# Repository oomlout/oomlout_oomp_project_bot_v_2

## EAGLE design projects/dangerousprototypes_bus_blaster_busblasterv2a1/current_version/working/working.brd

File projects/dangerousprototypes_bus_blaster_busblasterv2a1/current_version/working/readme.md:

# bus_blaster
 
## summary 
* id: dangerousprototypes_bus_blaster_busblasterv2a1
* user: dangerousprototypes
* name: bus_blaster
* board: busblasterv2a1
* repo: https://github.com/DangerousPrototypes/Bus_Blaster

* src_file_repo_sch: 
* src_file_repo_sch_link: https://github.com/DangerousPrototypes/Bus_Blaster/tree/master/
* full details link: https://github.com/oomlout/oomlout_oomp_project_bot_v_2/tree/main/projects/dangerousprototypes_bus_blaster_busblasterv2a1/current_version/working

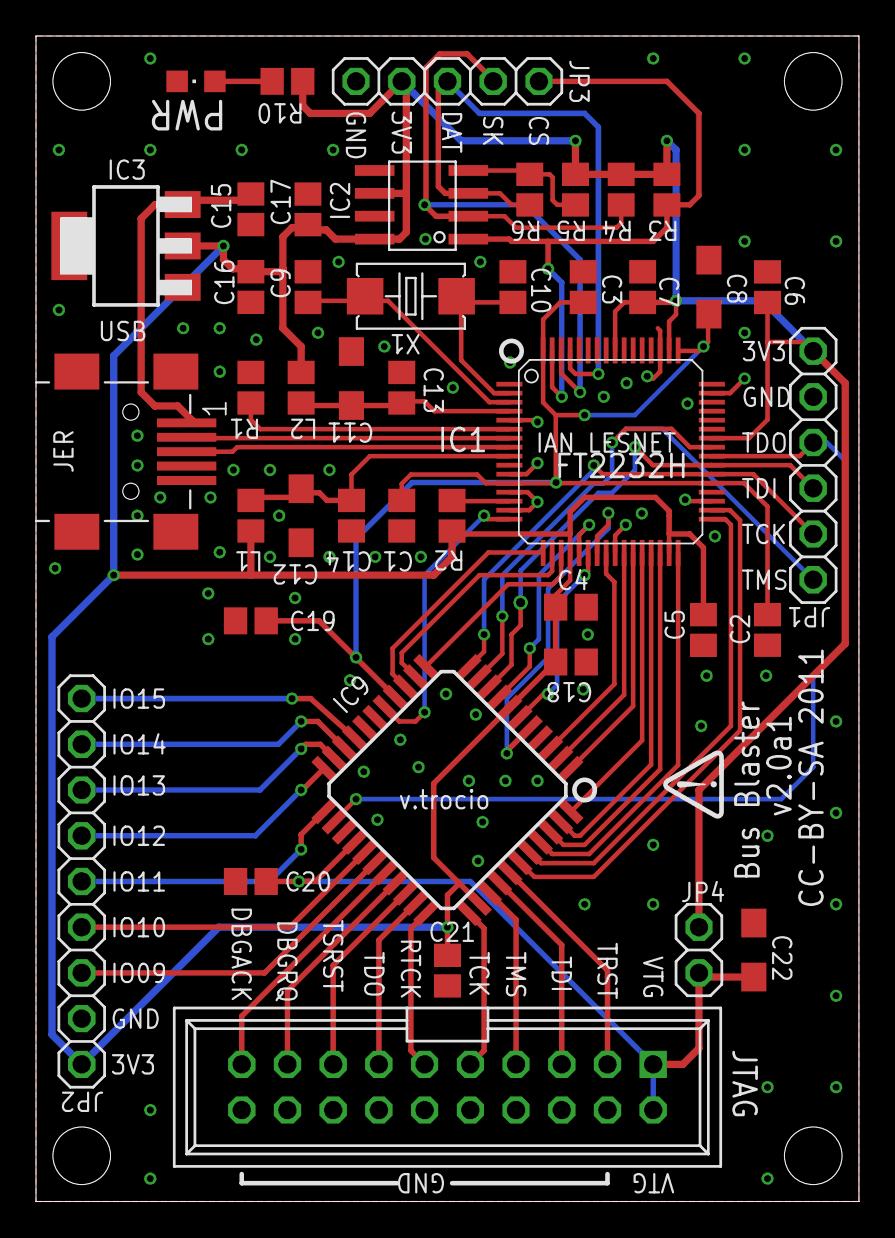
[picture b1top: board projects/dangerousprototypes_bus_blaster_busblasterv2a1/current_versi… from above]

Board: 2 copper layers, 45.7 x 64.8 mm, 45 parts (1 on the bottom side), 54 nets.

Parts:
C1, C2, C3, C4, C5, C6, C7, C13, C14, C15, C16, C17, C18, C19, C20, C21: 100nF; C805
C8: 3.3uF; SMC_A
C9, C10: 27pF; C805
C11, C12, C22: 4.7uF; SMC_A
IC1: FT2232H; LQFP64
IC2: 93C46; SOIC8
IC3: LD1117-3.3; SOT223
IC9: XC2C32A_VQ44_2; VQ44
JP1: 1X06
JP2: 1X09
JP3: 1X05
JP4: 1X02
JTAG: PINHEAD_-_COPY_PINSHRD_PTH_2X10
L1, L2: FB805
PWR: CHIPLED_0805
R1: 12K 1%; R805
R2: 1K; R805
R3, R4, R5: 10K; R805
R6: 2.2K; R805
R10: 470; R805
U$1, U$3: DP_LOGO
USB: CON-USB-MINI-BUSB1; CONN_USB_MINI-B
X1: 12MHz; 4X6

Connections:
1.8V: C1.2, C2.2, C3.2, C8.+, C19.2, IC1.12, IC1.37, IC1.49, IC1.64, IC9.15
+3V3: C4.2, C5.2, C6.2, C7.2, C16.2, C17.2, C18.1, C21.2, IC1.20, IC1.31, IC1.42, IC1.50, IC1.56, IC2.6, IC2.8, IC3.2, IC9.7, IC9.35, JP1.6, JP2.1, JP3.2, JP4.1, L1.2, L2.2, R2.1, R3.2, R4.2, R5.2, R10.2
AC0: IC1.26, IC9.2
AC1: IC1.27, IC9.1
AC2: IC1.28, IC9.44
AC3: IC1.29, IC9.43
AC4: IC1.30, IC9.42
AC5: IC1.32, IC9.41
AC6: IC1.33, IC9.40
AC7: IC1.34, IC9.39
AD0: IC1.16, IC9.16
AD1: IC1.17, IC9.14
AD2: IC1.18, IC9.13
AD3: IC1.19, IC9.12
AD4: IC1.21, IC9.8
AD5: IC1.22, IC9.6
AD6: IC1.23, IC9.5
AD7: IC1.24, IC9.3
BD0: IC1.38, IC9.11, JP1.2
BD1: IC1.39, IC9.9, JP1.3
BD2: IC1.40, IC9.24, JP1.4
BD3: IC1.41, IC9.10, JP1.1
CS: IC1.63, IC2.1, JP3.5, R3.1
DATA: IC1.61, IC2.3, JP3.3, R6.1
DBGACK1: IC9.29, JTAG.19
DBGRQ1: IC9.30, JTAG.17
DM: IC1.7, USB.D-
DO: IC2.4, R5.1, R6.2
DP: IC1.8, USB.D+
GND: C1.1, C2.1, C3.1, C4.1, C5.1, C6.1, C7.1, C8.-, C9.2, C10.2, C11.-, C12.-, C13.1, C14.1, C15.1, C16.1, C17.1, C18.2, C19.1, C20.1, C21.1, C22.-, IC1.1, IC1.5, IC1.10, IC1.11, IC1.13, IC1.15, IC1.25, IC1.35, IC1.47, IC1.51, IC2.5, IC2.7, IC3.1, IC9.4, IC9.17, IC9.18, IC9.25, JP1.5, JP2.2, JP3.1, JTAG.4, JTAG.6, JTAG.8, JTAG.10, JTAG.12, JTAG.14, JTAG.16, JTAG.18, JTAG.20, PWR.C, R1.1, USB.GND
IO9: IC9.28, JP2.3
IO10: IC9.27, JP2.4
IO11: IC9.23, JP2.5
IO12: IC9.22, JP2.6
IO13: IC9.21, JP2.7
IO14: IC9.20, JP2.8
IO15: IC9.19, JP2.9
unnamed: C9.1, IC1.3, X1.2
unnamed: C10.1, IC1.2, X1.1
unnamed: IC1.14, R2.2
unnamed: IC1.6, R1.2
unnamed: C15.2, IC3.3, USB.VUSB
unnamed: PWR.A, R10.1
RTCK1: IC9.33, JTAG.11
SK: IC1.62, IC2.2, JP3.4, R4.1
TCK1: IC9.34, JTAG.9
TDI1: IC9.37, JTAG.5
TDO1: IC9.32, JTAG.13
TMS1: IC9.36, JTAG.7
TRST1: IC9.38, JTAG.3
TSRST1: IC9.31, JTAG.15
VPHY: C11.+, C13.2, IC1.4, L2.1
VPLL: C12.+, C14.2, IC1.9, L1.1
V_TARGET: C20.2, C22.+, IC9.26, JP4.2, JTAG.1, JTAG.2

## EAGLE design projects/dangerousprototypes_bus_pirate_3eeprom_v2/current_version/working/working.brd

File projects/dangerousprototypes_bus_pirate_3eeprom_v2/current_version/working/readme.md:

# bus_pirate
 
## summary 
* id: dangerousprototypes_bus_pirate_3eeprom_v2
* user: dangerousprototypes
* name: bus_pirate
* board: 3eeprom_v2
* repo: https://github.com/DangerousPrototypes/Bus_Pirate

* src_file_repo_sch: 
* src_file_repo_sch_link: https://github.com/DangerousPrototypes/Bus_Pirate/tree/master/
* full details link: https://github.com/oomlout/oomlout_oomp_project_bot_v_2/tree/main/projects/dangerousprototypes_bus_pirate_3eeprom_v2/current_version/working

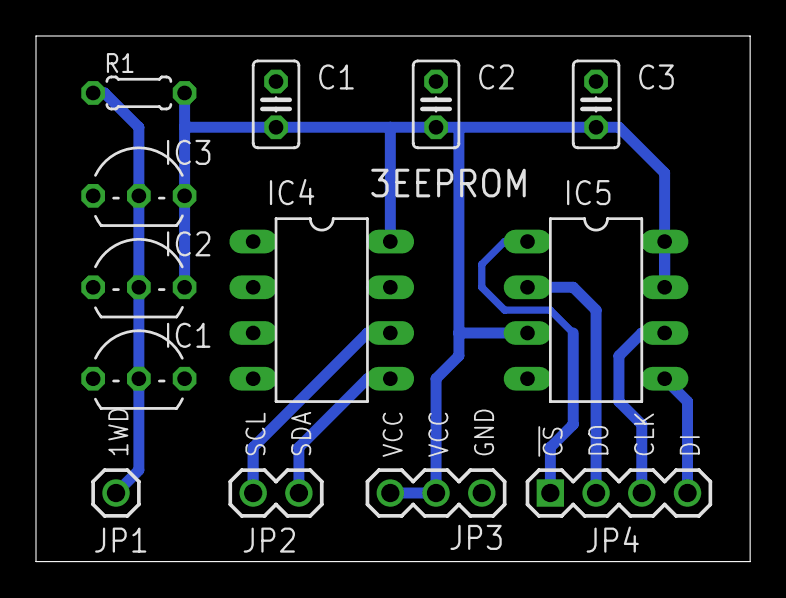
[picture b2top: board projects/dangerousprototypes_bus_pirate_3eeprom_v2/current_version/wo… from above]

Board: 2 copper layers, 39.7 x 29.2 mm, 13 parts (0 on the bottom side), 9 nets.

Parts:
C1, C2, C3: 0.1uF; C025-025X050
IC1: DS2431; TO92-
IC2, IC3: DS1822; TO92-
IC4: 24AAxx; DIL8
IC5: 25AAxx; DIL8
JP1: M01PTH; 1X01
JP2: 1X02
JP3: 1X03
JP4: 1X04
R1: 1K8; 0204/5

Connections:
+5V: C1.1, C2.1, C3.1, IC2.3, IC3.3, IC4.8, IC5.3, IC5.7, IC5.8, JP3.2, JP3.3, R1.2
GND: C1.2, C2.2, C3.2, IC1.1, IC2.1, IC3.1, IC4.1, IC4.2, IC4.3, IC4.4, IC4.7, IC5.4, JP3.1
unnamed: IC5.1, JP4.1
unnamed: IC5.2, JP4.2
unnamed: IC4.6, JP2.1
unnamed: IC4.5, JP2.2
unnamed: IC5.5, JP4.4
unnamed: IC5.6, JP4.3
unnamed: IC1.2, IC2.2, IC3.2, JP1.1, R1.1

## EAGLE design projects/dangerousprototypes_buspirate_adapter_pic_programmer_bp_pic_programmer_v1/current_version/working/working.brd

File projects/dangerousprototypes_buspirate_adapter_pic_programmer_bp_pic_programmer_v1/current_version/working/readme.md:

# buspirate_adapter_pic_programmer
 
## summary 
* id: dangerousprototypes_buspirate_adapter_pic_programmer_bp_pic_programmer_v1
* user: dangerousprototypes
* name: buspirate_adapter_pic_programmer
* board: bp_pic_programmer_v1
* repo: https://github.com/DangerousPrototypes/Buspirate_Adapter_Pic_Programmer

* src_file_repo_sch: 
* src_file_repo_sch_link: https://github.com/DangerousPrototypes/Buspirate_Adapter_Pic_Programmer/tree/master/
* full details link: https://github.com/oomlout/oomlout_oomp_project_bot_v_2/tree/main/projects/dangerousprototypes_buspirate_adapter_pic_programmer_bp_pic_programmer_v1/current_version/working

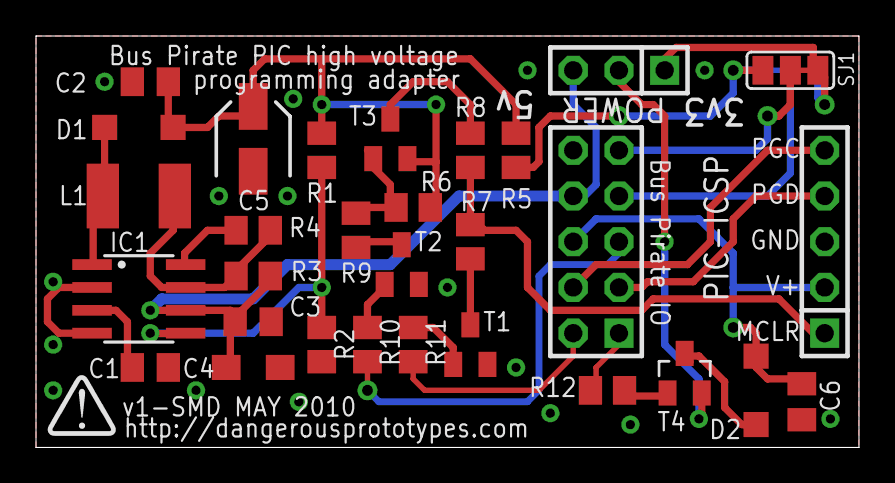
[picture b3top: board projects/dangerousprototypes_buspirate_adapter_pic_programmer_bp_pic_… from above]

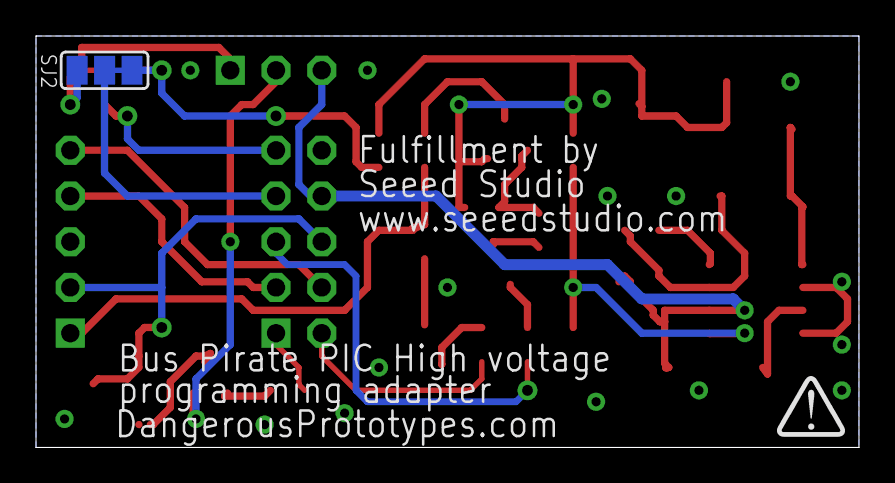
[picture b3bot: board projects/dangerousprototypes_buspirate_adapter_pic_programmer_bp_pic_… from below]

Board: 2 copper layers, 45.7 x 22.9 mm, 33 parts (2 on the bottom side), 28 nets.

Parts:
C1: 270pF; C0805K
C2, C6: 0.1uF/50V; C0805K
C3: 0.1uF; C0805K
C4: 10uF; SMC_A
C5: 4.7uF/35V; SANYO-OSCON_SMD_A5
D1, D2: 1N5819; SOD123
IC1: MC34063AD; SO08
JP1: 2X05
L1: 680uH/0.012A; L4532P
PIC-ICSP: 1X05
POWER: 1X03
R1: 20K; M0805
R2, R12: 2K2; M0805
R3: 4R7; M0805
R4: 180R; M0805
R5: 39K; M0805
R6: 100K; M0805
R7: 100R; M0805
R8, R9, R10, R11: 10K; M0805
SJ1, SJ2: SJ_2
T1, T2: BC818-16SMD; SOT23-BEC
T3: MMBTA56-SOT23; SOT23
T4: TSM2301CX; SOT23
U$1, U$2: DP-LOGO

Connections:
3V3: POWER.1, SJ1.3, SJ2.3
3V3(V3)ADC(V2GO): JP1.9, SJ1.2
5V: C3.1, C4.+, IC1.6, JP1.8, POWER.3, R3.1
13V: C2.1, C5.+, D1.C, R1.1, R5.2, R6.2, T3.2
ADC: R5.1, SJ1.1, SJ2.1
ADC(V3)3V3(V2GO): JP1.7, SJ2.2
GND: C1.2, C2.2, C3.2, C4.-, C5.-, C6.2, IC1.2, IC1.4, JP1.10, PIC-ICSP.3, R2.2, T1.E, T2.E
MCLR: JP1.2, R11.1
MISO: JP1.1, R12.1
unnamed: R12.2, T4.1
unnamed: R7.1, T1.C
unnamed: R8.2, T3.3
unnamed: R9.1, T2.C
unnamed: R6.1, R9.2, T3.1
unnamed: R11.2, T1.B
unnamed: R10.2, T2.B
unnamed: IC1.8, R4.1
unnamed: D2.A, T4.3
unnamed: IC1.7, L1.2, R3.2, R4.2
unnamed: IC1.5, R1.2, R2.1
unnamed: D1.A, IC1.1, L1.1
unnamed: C1.1, IC1.3
PGC: JP1.4, PIC-ICSP.5
PGD: JP1.3, PIC-ICSP.4
VDD_SWITCH: POWER.2, T4.2
VPP: PIC-ICSP.1, R7.2, R8.1
VPPEN: JP1.5, R10.1
VTARGET: C6.1, D2.C, JP1.6, PIC-ICSP.2

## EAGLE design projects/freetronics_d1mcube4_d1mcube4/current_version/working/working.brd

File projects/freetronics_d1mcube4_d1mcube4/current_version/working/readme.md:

# d1mcube4
 
## summary 
* id: freetronics_d1mcube4_d1mcube4
* user: freetronics
* name: d1mcube4
* board: d1mcube4
* repo: https://github.com/freetronics/D1MCUBE4

* src_file_repo_sch: 
* src_file_repo_sch_link: https://github.com/freetronics/D1MCUBE4/tree/master/
* full details link: https://github.com/oomlout/oomlout_oomp_project_bot_v_2/tree/main/projects/freetronics_d1mcube4_d1mcube4/current_version/working

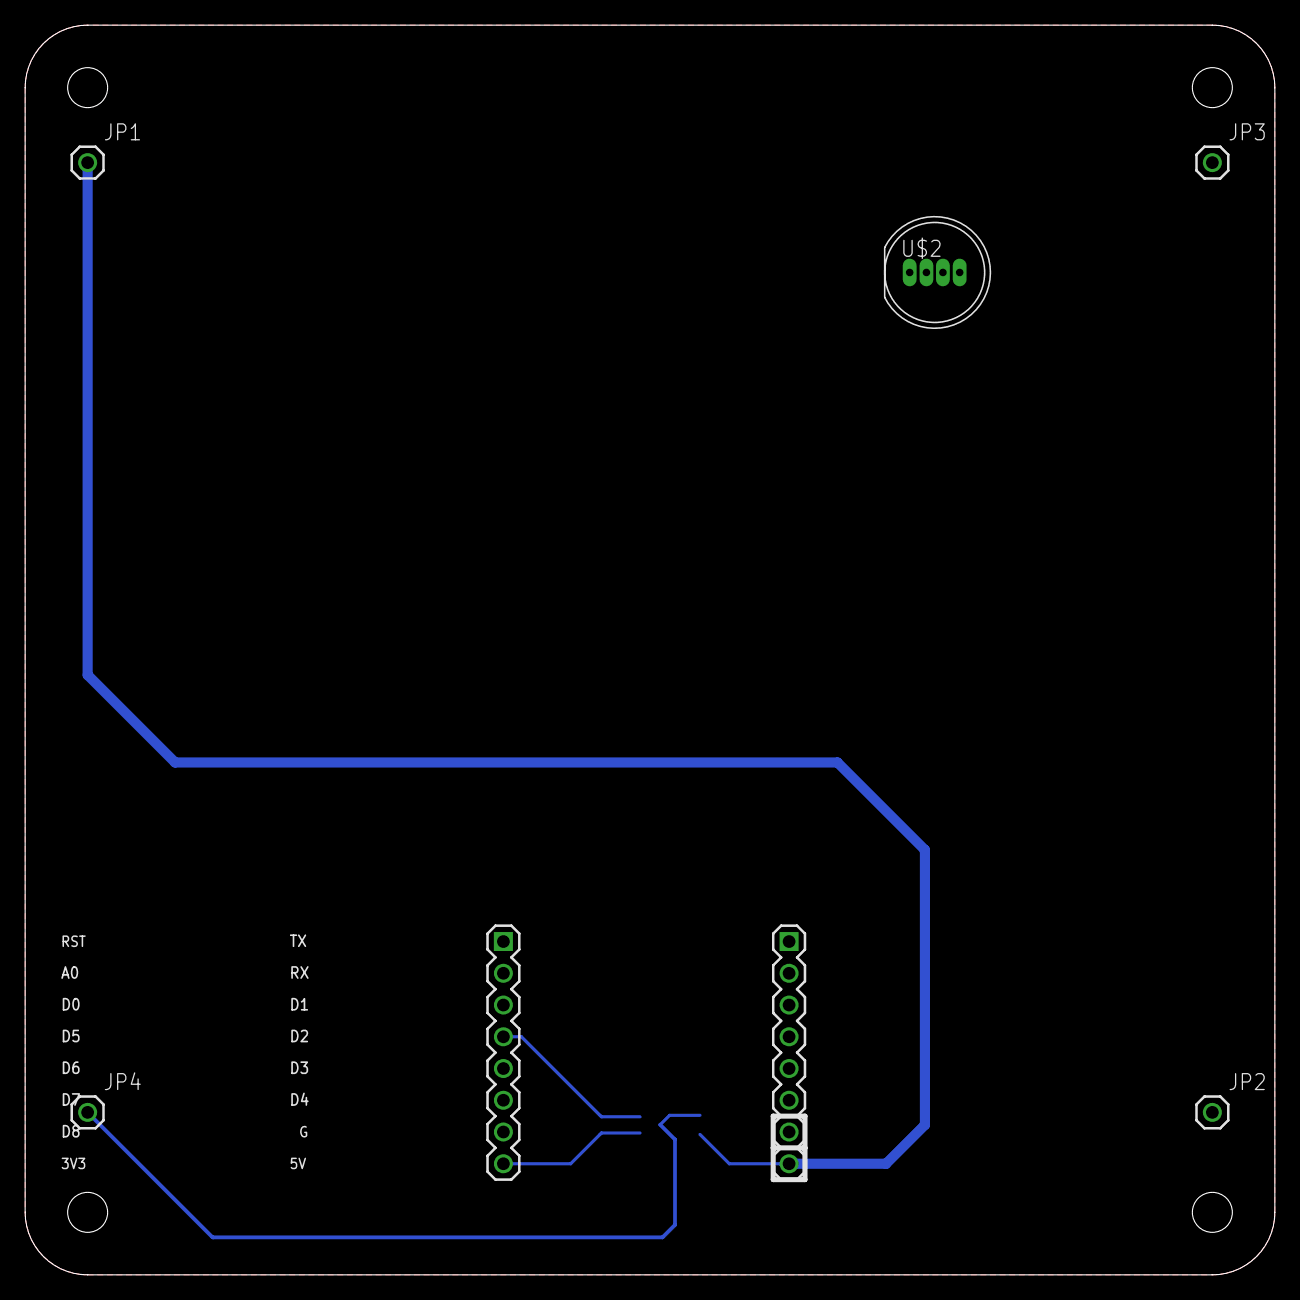
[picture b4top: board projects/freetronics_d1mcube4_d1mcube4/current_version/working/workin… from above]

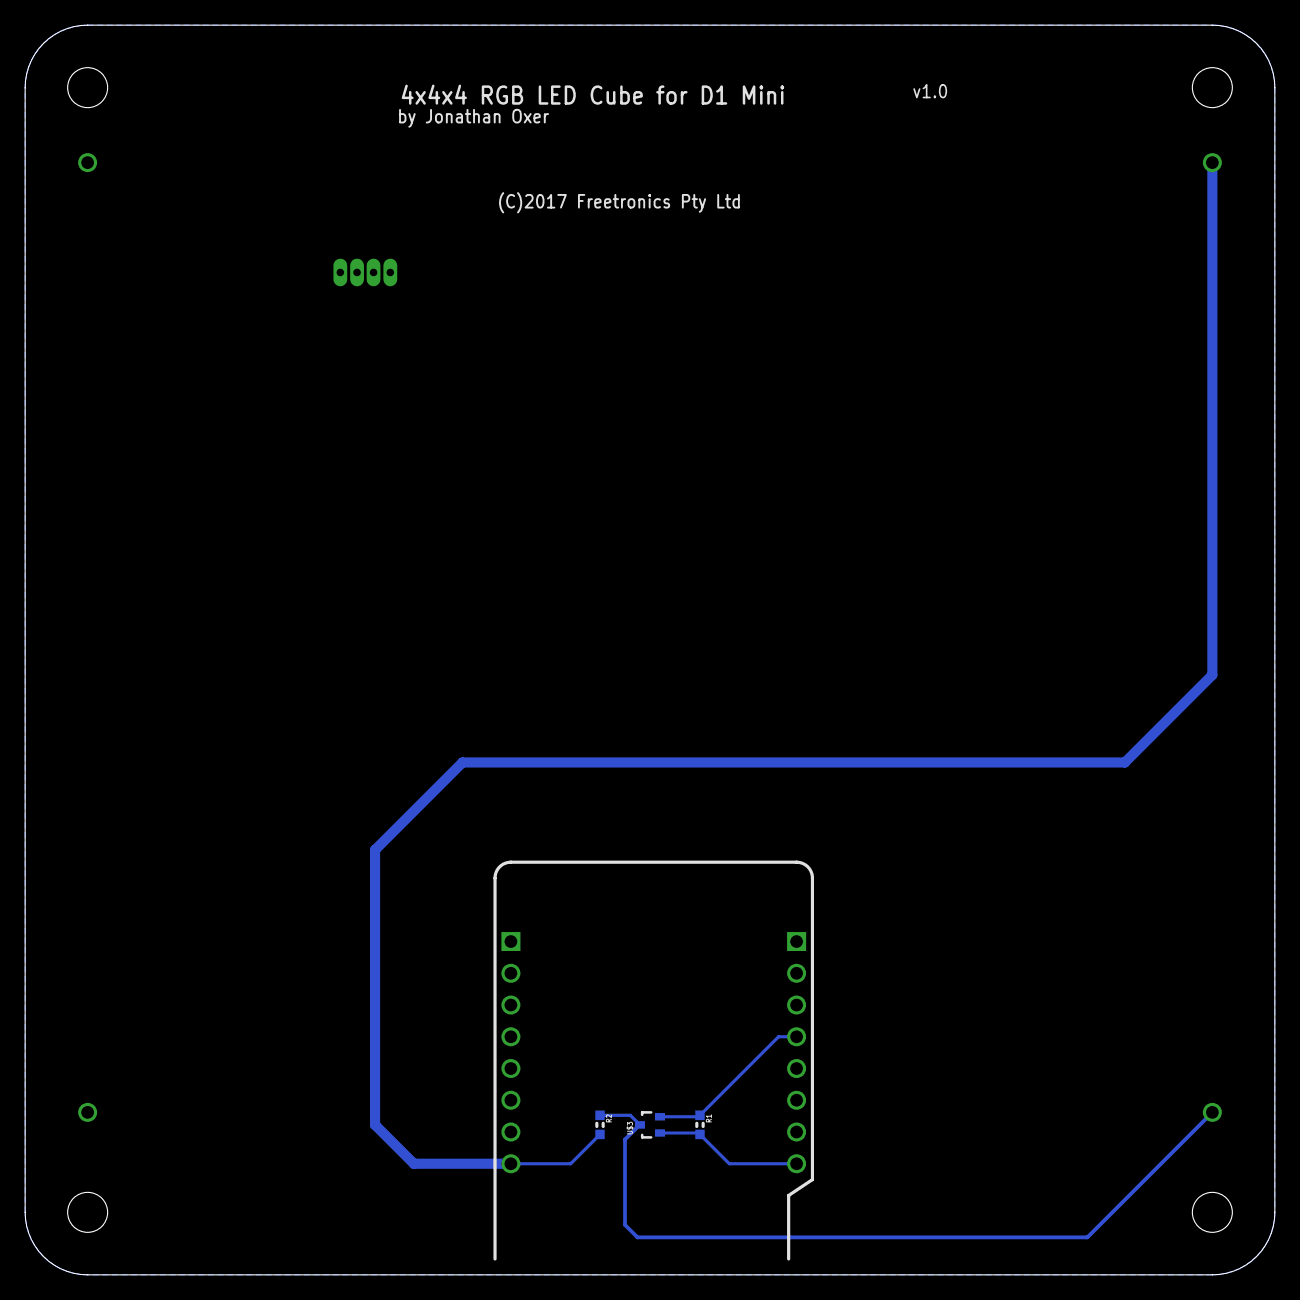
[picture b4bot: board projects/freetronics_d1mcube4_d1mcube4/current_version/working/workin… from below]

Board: 2 copper layers, 100.0 x 100.0 mm, 10 parts (3 on the bottom side), 5 nets.

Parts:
H1, H2: 1X08
JP1, JP2, JP3, JP4: M01PTH; 1X01
R1, R2: 10k; 0603
U$2: APA106F8; LED8MMRGB
U$3: RJU003N03; SOT32-3

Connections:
3.3V: H1.8, R1.2, U$3.1
5V: H2.8, JP1.1, R2.2
D5: H1.4, R1.1, U$3.2
DATA: JP4.1, R2.1, U$3.3
GND: H2.7, JP2.1, JP3.1, U$2.2

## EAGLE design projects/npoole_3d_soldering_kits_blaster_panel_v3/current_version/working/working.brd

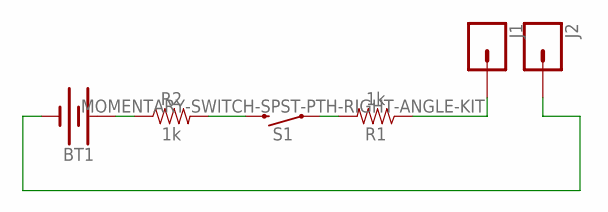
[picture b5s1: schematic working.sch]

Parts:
BT1: BATTERY-20MM_SMD_4LEGS; BATTCON_20MM_4LEGS
J1, J2: CONN_01; 1X01
R1, R2: 1k; AXIAL-0.3
S1: MOMENTARY-SWITCH-SPST-PTH-RIGHT-ANGLE-KIT; TACTILE_SWITCH_PTH_RIGHT_ANGLE_KIT

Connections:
unnamed: R2.P$2 (2), S1.2
unnamed: R1.P$2 (2), S1.1
unnamed: J1.1, R1.P$1 (1)
unnamed: BT1.NEGATIVE (-), J2.1
unnamed: BT1.POSITIVE@1 (+), BT1.POSITIVE@2 (+), BT1.POSITIVE@3 (+), BT1.POSITIVE@4 (+), R2.P$1 (1)

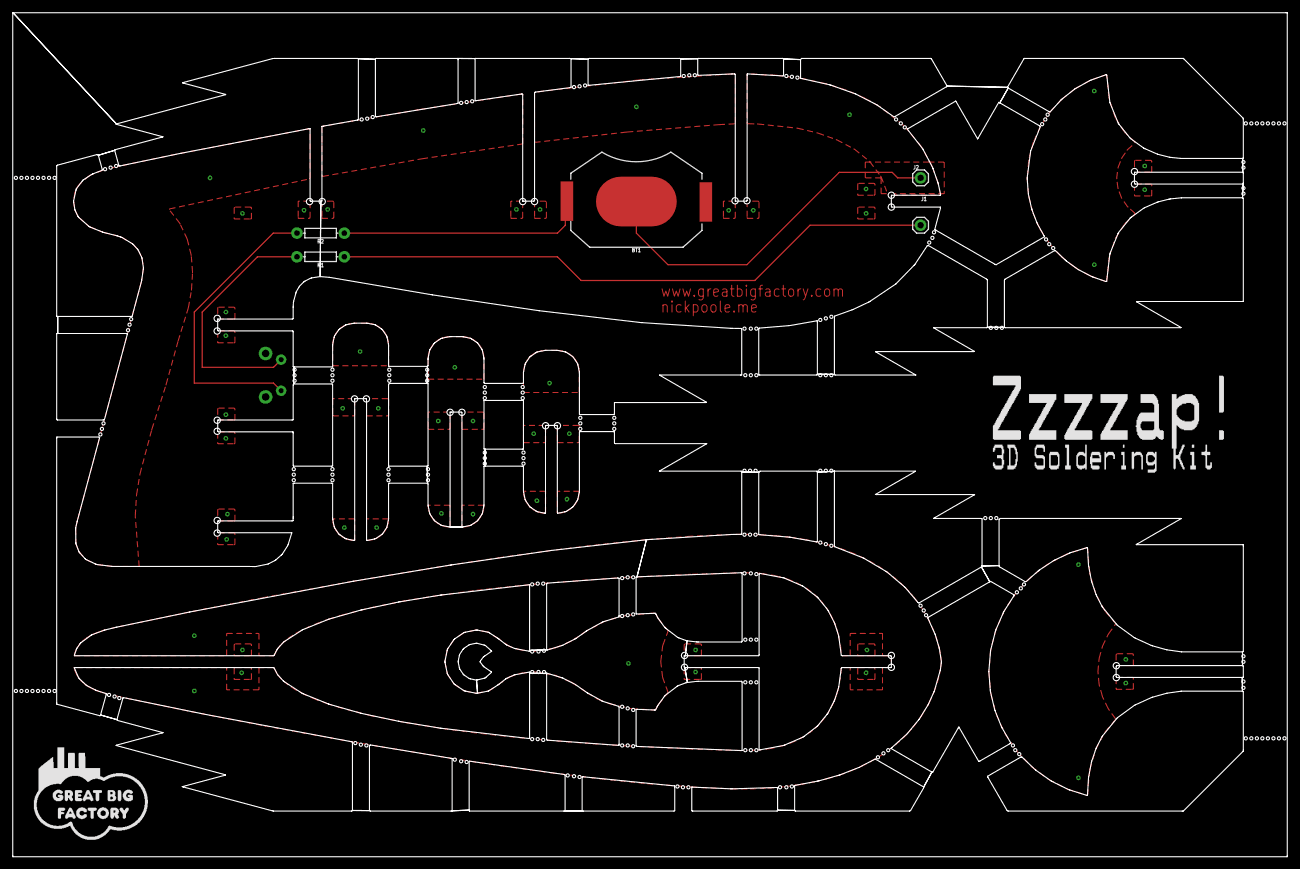
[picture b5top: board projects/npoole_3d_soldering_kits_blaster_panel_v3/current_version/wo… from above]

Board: 2 copper layers, 205.0 x 135.8 mm, 8 parts (1 on the bottom side), 5 nets.

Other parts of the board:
E$1: GREATBIGFACTORYCLOUDLOGO#PNG
U$1: TEXT345#PNG

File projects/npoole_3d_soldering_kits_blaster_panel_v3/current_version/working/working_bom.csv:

"Id";"Designator";"Footprint";"Quantity";"Designation";"Supplier and ref";
1;"@HOLE20,@HOLE8,@HOLE134,@HOLE54,@HOLE166,@HOLE176,@HOLE216,@HOLE157,@HOLE70,@HOLE173,@HOLE236,@HOLE16,@HOLE103,@HOLE145,@HOLE208,@HOLE147,@HOLE37,@HOLE184,@HOLE240,@HOLE138,@HOLE17,@HOLE44,@HOLE24,@HOLE28,@HOLE160,@HOLE117,@HOLE25,@HOLE74,@HOLE239,@HOLE217,@HOLE214,@HOLE213,@HOLE237,@HOLE82,@HOLE142,@HOLE120,@HOLE137,@HOLE234,@HOLE39,@HOLE152,@HOLE66,@HOLE95,@HOLE194,@HOLE198,@HOLE182,@HOLE185,@HOLE193,@HOLE121,@HOLE87,@HOLE215,@HOLE183,@HOLE12,@HOLE69,@HOLE62,@HOLE132,@HOLE211,@HOLE169,@HOLE190,@HOLE94,@HOLE90,@HOLE104,@HOLE158,@HOLE33,@HOLE68,@HOLE0,@HOLE45,@HOLE57,@HOLE238,@HOLE170,@HOLE21,@HOLE187,@HOLE92,@HOLE77,@HOLE151,@HOLE123,@HOLE72,@HOLE52,@HOLE226,@HOLE202,@HOLE210,@HOLE65,@HOLE110,@HOLE206,@HOLE212,@HOLE18,@HOLE186,@HOLE47,@HOLE203,@HOLE165,@HOLE177,@HOLE75,@HOLE15,@HOLE23,@HOLE153,@HOLE84,@HOLE81,@HOLE108,@HOLE107,@HOLE150,@HOLE136,@HOLE11,@HOLE163,@HOLE10,@HOLE31,@HOLE48,@HOLE83,@HOLE96,@HOLE178,@HOLE9,@HOLE101,@HOLE102,@HOLE241,@HOLE51,@HOLE223,@HOLE172,@HOLE122,@HOLE219,@HOLE209,@HOLE7,@HOLE116,@HOLE56,@HOLE105,@HOLE118,@HOLE34,@HOLE38,@HOLE235,@HOLE230,@HOLE231,@HOLE164,@HOLE97,@HOLE40,@HOLE127,@HOLE124,@HOLE205,@HOLE168,@HOLE115,@HOLE2,@HOLE80,@HOLE29,@HOLE144,@HOLE159,@HOLE3,@HOLE106,@HOLE53,@HOLE61,@HOLE155,@HOLE200,@HOLE35,@HOLE4,@HOLE228,@HOLE148,@HOLE196,@HOLE207,@HOLE129,@HOLE146,@HOLE125,@HOLE218,@HOLE119,@HOLE175,@HOLE130,@HOLE59,@HOLE233,@HOLE63,@HOLE191,@HOLE13,@HOLE201,@HOLE86,@HOLE181,@HOLE100,@HOLE154,@HOLE131,@HOLE220,@HOLE67,@HOLE99,@HOLE41,@HOLE180,@HOLE188,@HOLE171,@HOLE46,@HOLE1,@HOLE76,@HOLE204,@HOLE174,@HOLE128,@HOLE71,@HOLE197,@HOLE98,@HOLE222,@HOLE79,@HOLE232,@HOLE30,@HOLE93,@HOLE14,@HOLE64,@HOLE162,@HOLE161,@HOLE139,@HOLE135,@HOLE224,@HOLE88,@HOLE89,@HOLE78,@HOLE91,@HOLE227,@HOLE32,@HOLE195,@HOLE26,@HOLE126,@HOLE27,@HOLE36,@HOLE60,@HOLE199,@HOLE192,@HOLE114,@HOLE133,@HOLE189,@HOLE42,@HOLE167,@HOLE225,@HOLE111,@HOLE141,@HOLE49,@HOLE179,@HOLE85,@HOLE112,@HOLE221,@HOLE149,@HOLE113,@HOLE55,@HOLE109,@HOLE19,@HOLE50,@HOLE73,@HOLE156,@HOLE6,@HOLE58,@HOLE143,@HOLE140,@HOLE43,@HOLE5,@HOLE229,@HOLE22";"";242;"";;;
2;"J2,J1";"1X01";2;"";;;
3;"E$1";"GREATBIGFACTORYCLOUDLOGO#PNG";1;"";;;
4;"U$1";"TEXT345#PNG";1;"";;;
5;"R1,R2";"AXIAL-0.3";2;"1k";;;
6;"BT1";"BATTCON_20MM_4LEGS";1;"";;;
7;"S1";"TACTILE_SWITCH_PTH_RIGHT_ANGLE_KIT";1;"MOMENTARY-SWITCH-SPST-PTH-RIGHT-ANGLE-KIT";;;

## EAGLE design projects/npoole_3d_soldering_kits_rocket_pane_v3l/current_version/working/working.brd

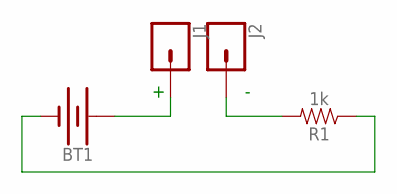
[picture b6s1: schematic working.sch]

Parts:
BT1: BATTERY-20MM_SMD_4LEGS; BATTCON_20MM_4LEGS
J1, J2: CONN_01; 1X01
R1: 1k; AXIAL-0.3

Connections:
unnamed: BT1.POSITIVE@1 (+), BT1.POSITIVE@2 (+), BT1.POSITIVE@3 (+), BT1.POSITIVE@4 (+), J1.1
unnamed: J2.1, R1.P$2 (2)
unnamed: BT1.NEGATIVE (-), R1.P$1 (1)

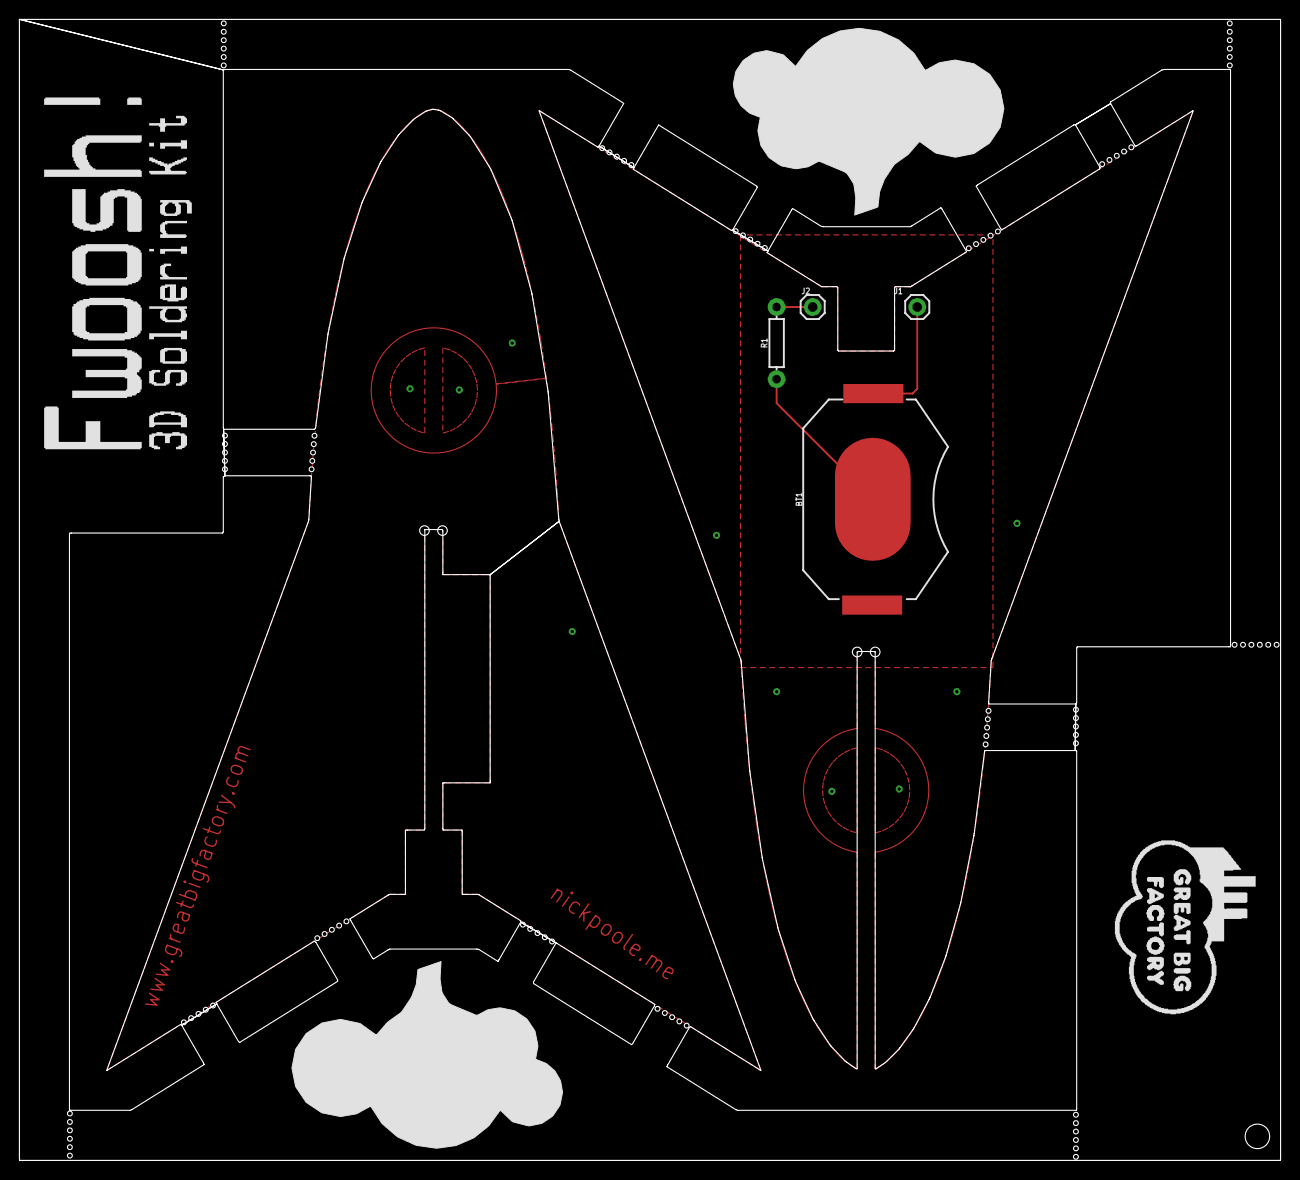
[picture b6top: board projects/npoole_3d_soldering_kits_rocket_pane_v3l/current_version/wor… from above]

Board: 2 copper layers, 133.3 x 120.6 mm, 6 parts (0 on the bottom side), 3 nets.

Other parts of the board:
U$1: TEXT1466#PNG
U$2: GREATBIGFACTORYCLOUDLOGO#PNG

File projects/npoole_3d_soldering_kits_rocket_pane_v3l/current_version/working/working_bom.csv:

"Id";"Designator";"Footprint";"Quantity";"Designation";"Supplier and ref";
1;"@HOLE72,@HOLE63,@HOLE25,@HOLE85,@HOLE20,@HOLE17,@HOLE7,@HOLE42,@HOLE31,@HOLE70,@HOLE1,@HOLE32,@HOLE18,@HOLE49,@HOLE12,@HOLE64,@HOLE8,@HOLE89,@HOLE59,@HOLE4,@HOLE30,@HOLE29,@HOLE9,@HOLE80,@HOLE23,@HOLE83,@HOLE2,@HOLE33,@HOLE60,@HOLE41,@HOLE82,@HOLE56,@HOLE0,@HOLE90,@HOLE77,@HOLE19,@HOLE10,@HOLE43,@HOLE22,@HOLE15,@HOLE62,@HOLE58,@HOLE73,@HOLE57,@HOLE36,@HOLE27,@HOLE75,@HOLE66,@HOLE92,@HOLE45,@HOLE13,@HOLE94,@HOLE81,@HOLE68,@HOLE44,@HOLE3,@HOLE87,@HOLE24,@HOLE38,@HOLE61,@HOLE35,@HOLE88,@HOLE34,@HOLE76,@HOLE37,@HOLE11,@HOLE71,@HOLE5,@HOLE78,@HOLE53,@HOLE93,@HOLE28,@HOLE6,@HOLE54,@HOLE48,@HOLE51,@HOLE50,@HOLE79,@HOLE69,@HOLE84,@HOLE52,@HOLE91,@HOLE39,@HOLE47,@HOLE74,@HOLE21,@HOLE14,@HOLE65,@HOLE67,@HOLE16,@HOLE55,@HOLE40,@HOLE46,@HOLE86,@HOLE26";"";95;"";;;
2;"J1,J2";"1X01";2;"";;;
3;"U$1";"TEXT1466#PNG";1;"";;;
4;"U$2";"GREATBIGFACTORYCLOUDLOGO#PNG";1;"";;;
5;"R1";"AXIAL-0.3";1;"1k";;;
6;"BT1";"BATTCON_20MM_4LEGS";1;"";;;

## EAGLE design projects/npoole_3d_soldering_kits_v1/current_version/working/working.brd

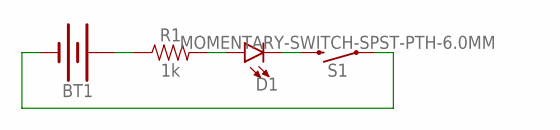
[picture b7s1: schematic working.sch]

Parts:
BT1: BATTERY-20MM_SMD_4LEGS; BATTCON_20MM_4LEGS
D1: LED5MM; LED_5MM
R1: 1k; AXIAL-0.3
S1: MOMENTARY-SWITCH-SPST-PTH-6.0MM; TACTILE_SWITCH_PTH_6.0MM

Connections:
unnamed: BT1.POSITIVE@1 (+), BT1.POSITIVE@2 (+), BT1.POSITIVE@3 (+), BT1.POSITIVE@4 (+), R1.P$1 (1)
unnamed: D1.A, R1.P$2 (2)
unnamed: D1.K (C), S1.3 (2)
unnamed: BT1.NEGATIVE (-), S1.1

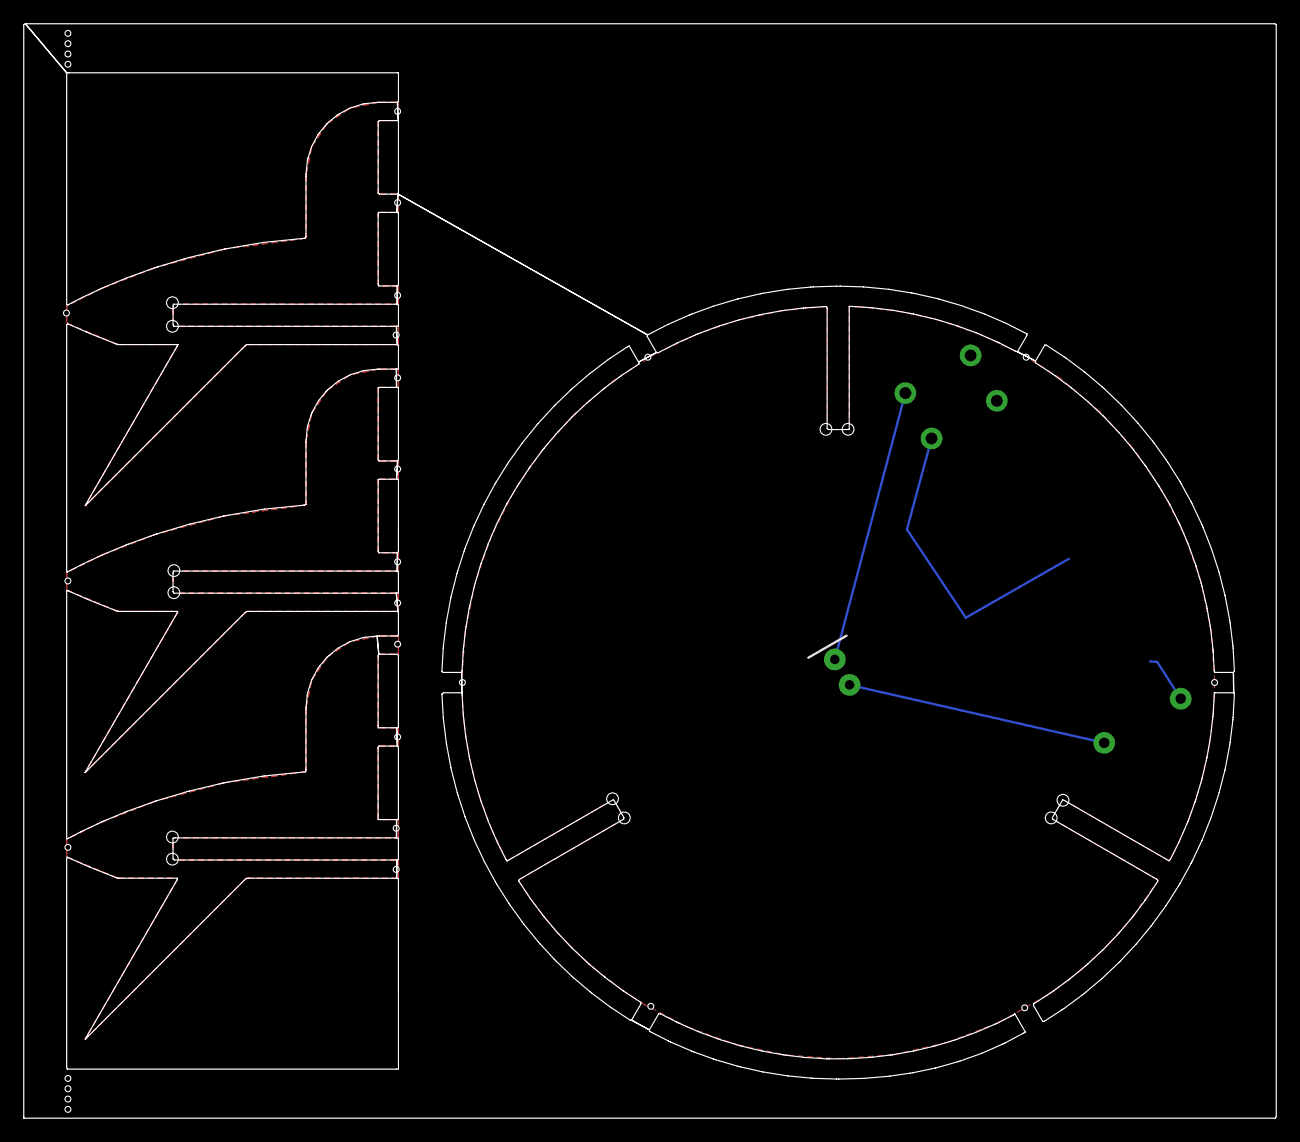
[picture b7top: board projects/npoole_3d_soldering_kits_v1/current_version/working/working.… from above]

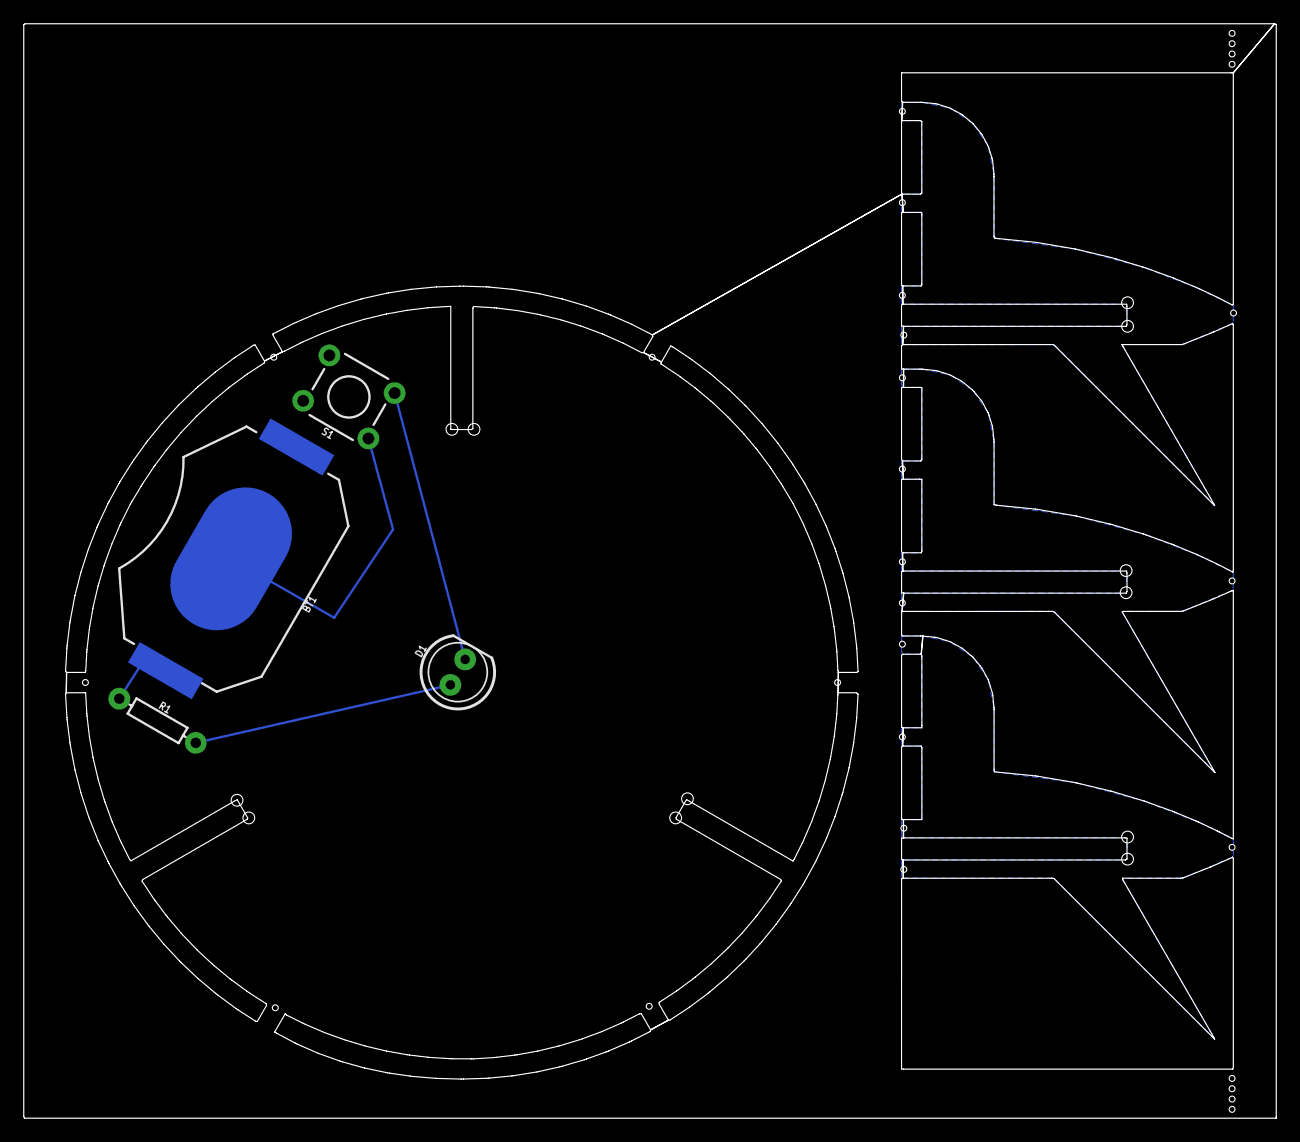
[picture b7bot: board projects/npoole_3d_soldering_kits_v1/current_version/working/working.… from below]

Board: 2 copper layers, 108.1 x 94.4 mm, 4 parts (4 on the bottom side), 4 nets.

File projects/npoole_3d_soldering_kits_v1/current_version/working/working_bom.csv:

"Id";"Designator";"Footprint";"Quantity";"Designation";"Supplier and ref";
1;"@HOLE23,@HOLE17,@HOLE12,@HOLE29,@HOLE19,@HOLE13,@HOLE5,@HOLE38,@HOLE14,@HOLE3,@HOLE24,@HOLE22,@HOLE34,@HOLE37,@HOLE21,@HOLE36,@HOLE39,@HOLE4,@HOLE11,@HOLE33,@HOLE25,@HOLE28,@HOLE27,@HOLE10,@HOLE15,@HOLE1,@HOLE30,@HOLE2,@HOLE35,@HOLE0,@HOLE32,@HOLE31,@HOLE8,@HOLE7,@HOLE9,@HOLE18,@HOLE40,@HOLE6,@HOLE16,@HOLE20,@HOLE26";"";41;"";;;
2;"BT1";"BATTCON_20MM_4LEGS";1;"";;;
3;"R1";"AXIAL-0.3";1;"1k";;;
4;"D1";"LED_5MM";1;"";;;
5;"S1";"TACTILE_SWITCH_PTH_6.0MM";1;"MOMENTARY-SWITCH-SPST-PTH-6.0MM";;;

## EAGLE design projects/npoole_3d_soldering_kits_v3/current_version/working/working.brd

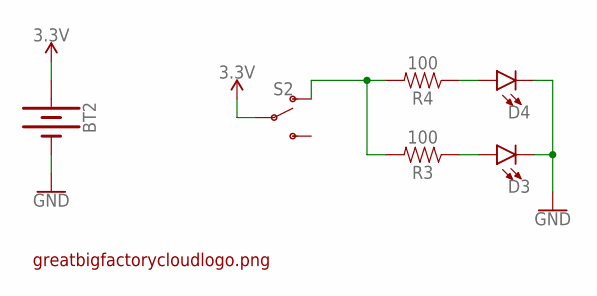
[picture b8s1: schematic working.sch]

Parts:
BT2: BATTERY-20MM_PTH_KIT; BATTCOM_20MM_PTH_KIT
D3, D4: LED5MM; LED_5MM
R3, R4: 100; AXIAL-0.3EZ
S2: SWITCH-SPDT-PTH-11.6X4.0MM-KIT; SWITCH_SPDT_PTH_11.6X4.0MM_KIT
U$1: GREATBIGFACTORYCLOUDLOGO#PNG

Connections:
3.3V: BT2.1 (+), S2.2
GND: BT2.2 (-), D3.K (C), D4.K (C)
unnamed: R3.P$2 (2), R4.P$2 (2), S2.1 (O)
unnamed: D4.A, R4.P$1 (1)
unnamed: D3.A, R3.P$1 (1)

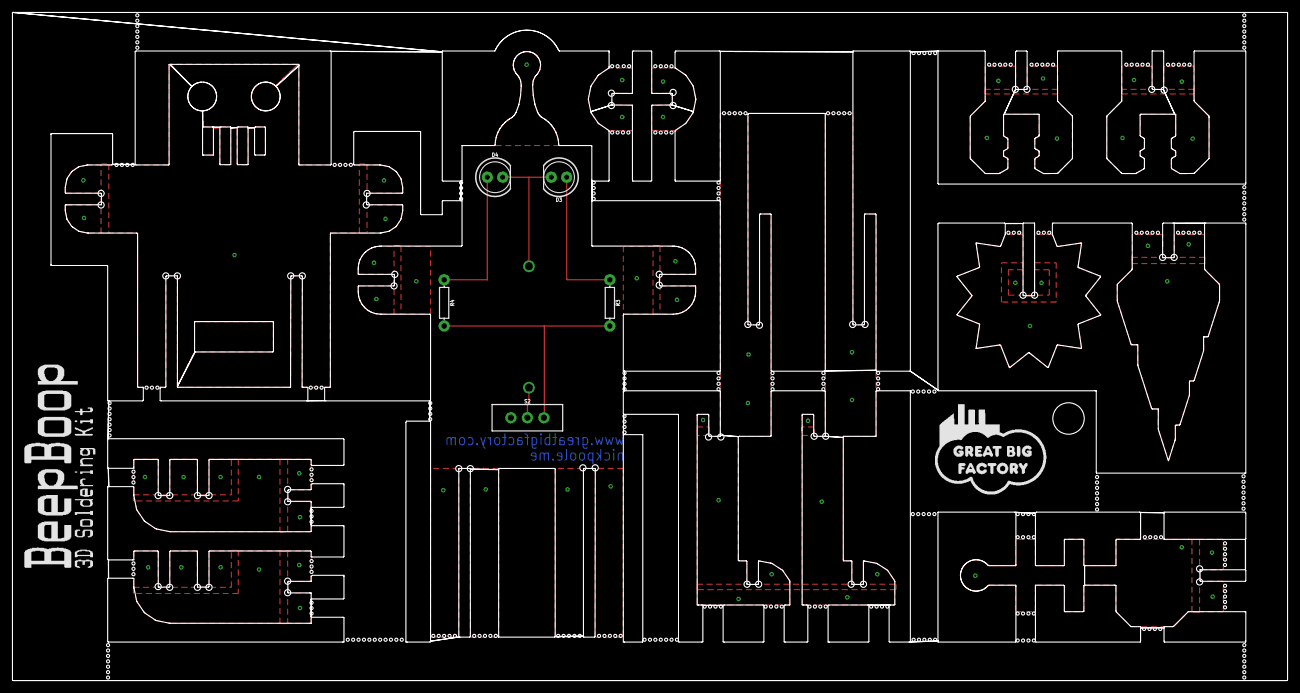
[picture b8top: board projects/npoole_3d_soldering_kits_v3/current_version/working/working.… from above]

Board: 2 copper layers, 210.1 x 110.1 mm, 8 parts (1 on the bottom side), 5 nets.

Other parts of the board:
U$2: RECT1468#PNG

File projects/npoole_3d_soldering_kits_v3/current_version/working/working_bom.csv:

"Id";"Designator";"Footprint";"Quantity";"Designation";"Supplier and ref";
1;"@HOLE198,@HOLE122,@HOLE124,@HOLE74,@HOLE68,@HOLE293,@HOLE29,@HOLE268,@HOLE221,@HOLE226,@HOLE330,@HOLE295,@HOLE11,@HOLE0,@HOLE292,@HOLE49,@HOLE169,@HOLE306,@HOLE328,@HOLE65,@HOLE195,@HOLE93,@HOLE17,@HOLE213,@HOLE69,@HOLE199,@HOLE212,@HOLE339,@HOLE319,@HOLE321,@HOLE345,@HOLE323,@HOLE96,@HOLE190,@HOLE119,@HOLE149,@HOLE239,@HOLE55,@HOLE252,@HOLE281,@HOLE249,@HOLE51,@HOLE137,@HOLE34,@HOLE223,@HOLE6,@HOLE318,@HOLE114,@HOLE154,@HOLE176,@HOLE66,@HOLE23,@HOLE151,@HOLE141,@HOLE348,@HOLE121,@HOLE326,@HOLE184,@HOLE274,@HOLE225,@HOLE344,@HOLE165,@HOLE88,@HOLE83,@HOLE217,@HOLE276,@HOLE110,@HOLE234,@HOLE331,@HOLE204,@HOLE336,@HOLE316,@HOLE286,@HOLE75,@HOLE16,@HOLE76,@HOLE206,@HOLE220,@HOLE258,@HOLE333,@HOLE216,@HOLE174,@HOLE25,@HOLE7,@HOLE296,@HOLE56,@HOLE39,@HOLE235,@HOLE73,@HOLE192,@HOLE191,@HOLE325,@HOLE92,@HOLE297,@HOLE134,@HOLE289,@HOLE143,@HOLE243,@HOLE130,@HOLE131,@HOLE311,@HOLE236,@HOLE257,@HOLE32,@HOLE324,@HOLE327,@HOLE218,@HOLE335,@HOLE260,@HOLE85,@HOLE123,@HOLE244,@HOLE248,@HOLE167,@HOLE26,@HOLE282,@HOLE41,@HOLE105,@HOLE44,@HOLE322,@HOLE70,@HOLE147,@HOLE175,@HOLE80,@HOLE156,@HOLE181,@HOLE253,@HOLE47,@HOLE72,@HOLE201,@HOLE37,@HOLE126,@HOLE273,@HOLE15,@HOLE270,@HOLE298,@HOLE310,@HOLE1,@HOLE22,@HOLE303,@HOLE254,@HOLE67,@HOLE351,@HOLE132,@HOLE307,@HOLE205,@HOLE152,@HOLE118,@HOLE317,@HOLE62,@HOLE84,@HOLE271,@HOLE78,@HOLE247,@HOLE64,@HOLE229,@HOLE101,@HOLE30,@HOLE280,@HOLE340,@HOLE211,@HOLE179,@HOLE71,@HOLE54,@HOLE3,@HOLE230,@HOLE48,@HOLE86,@HOLE278,@HOLE99,@HOLE103,@HOLE180,@HOLE28,@HOLE309,@HOLE133,@HOLE148,@HOLE238,@HOLE104,@HOLE46,@HOLE241,@HOLE50,@HOLE97,@HOLE102,@HOLE188,@HOLE337,@HOLE117,@HOLE285,@HOLE136,@HOLE266,@HOLE43,@HOLE269,@HOLE5,@HOLE246,@HOLE82,@HOLE349,@HOLE170,@HOLE187,@HOLE145,@HOLE129,@HOLE203,@HOLE263,@HOLE178,@HOLE305,@HOLE304,@HOLE127,@HOLE262,@HOLE272,@HOLE341,@HOLE125,@HOLE202,@HOLE163,@HOLE287,@HOLE251,@HOLE87,@HOLE312,@HOLE231,@HOLE94,@HOLE291,@HOLE222,@HOLE294,@HOLE31,@HOLE95,@HOLE33,@HOLE320,@HOLE106,@HOLE259,@HOLE255,@HOLE347,@HOLE208,@HOLE290,@HOLE210,@HOLE140,@HOLE334,@HOLE207,@HOLE302,@HOLE279,@HOLE250,@HOLE45,@HOLE177,@HOLE314,@HOLE267,@HOLE40,@HOLE299,@HOLE135,@HOLE57,@HOLE91,@HOLE242,@HOLE18,@HOLE313,@HOLE162,@HOLE52,@HOLE35,@HOLE265,@HOLE329,@HOLE301,@HOLE21,@HOLE308,@HOLE160,@HOLE100,@HOLE115,@HOLE107,@HOLE338,@HOLE300,@HOLE108,@HOLE90,@HOLE166,@HOLE197,@HOLE142,@HOLE79,@HOLE228,@HOLE81,@HOLE10,@HOLE193,@HOLE346,@HOLE168,@HOLE315,@HOLE27,@HOLE158,@HOLE240,@HOLE350,@HOLE264,@HOLE98,@HOLE36,@HOLE342,@HOLE144,@HOLE111,@HOLE128,@HOLE164,@HOLE12,@HOLE61,@HOLE185,@HOLE58,@HOLE209,@HOLE138,@HOLE146,@HOLE237,@HOLE2,@HOLE277,@HOLE60,@HOLE113,@HOLE13,@HOLE8,@HOLE63,@HOLE183,@HOLE283,@HOLE4,@HOLE196,@HOLE9,@HOLE214,@HOLE219,@HOLE89,@HOLE172,@HOLE150,@HOLE288,@HOLE224,@HOLE186,@HOLE53,@HOLE59,@HOLE256,@HOLE284,@HOLE157,@HOLE332,@HOLE24,@HOLE227,@HOLE20,@HOLE112,@HOLE171,@HOLE116,@HOLE14,@HOLE38,@HOLE194,@HOLE161,@HOLE109,@HOLE159,@HOLE120,@HOLE233,@HOLE215,@HOLE200,@HOLE343,@HOLE42,@HOLE261,@HOLE275,@HOLE189,@HOLE77,@HOLE153,@HOLE139,@HOLE182,@HOLE155,@HOLE173,@HOLE19,@HOLE232,@HOLE245";"";352;"";;;
2;"U$2";"RECT1468#PNG";1;"";;;
3;"U$1";"GREATBIGFACTORYCLOUDLOGO#PNG";1;"GREATBIGFACTORYCLOUDLOGO#PNG";;;
4;"D3,D4";"LED_5MM";2;"";;;
5;"S2";"SWITCH_SPDT_PTH_11.6X4.0MM_KIT";1;"";;;
6;"R4,R3";"AXIAL-0.3EZ";2;"100";;;
7;"BT2";"BATTCOM_20MM_PTH_KIT";1;"";;;

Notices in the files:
projects/freetronics_d1mcube4_d1mcube4/current_version/working/working.brd:
(C)2017 Freetronics Pty Ltd
parts and their libraries:
freetronics-original: Licensing: CC v3.0 Share-Alike You are welcome to use this library for commercial purposes.
SparkFun-Batteries: Licensing: Creative Commons ShareAlike 4.0 International - https://creativecommons.org/licenses/by-sa/4.0
